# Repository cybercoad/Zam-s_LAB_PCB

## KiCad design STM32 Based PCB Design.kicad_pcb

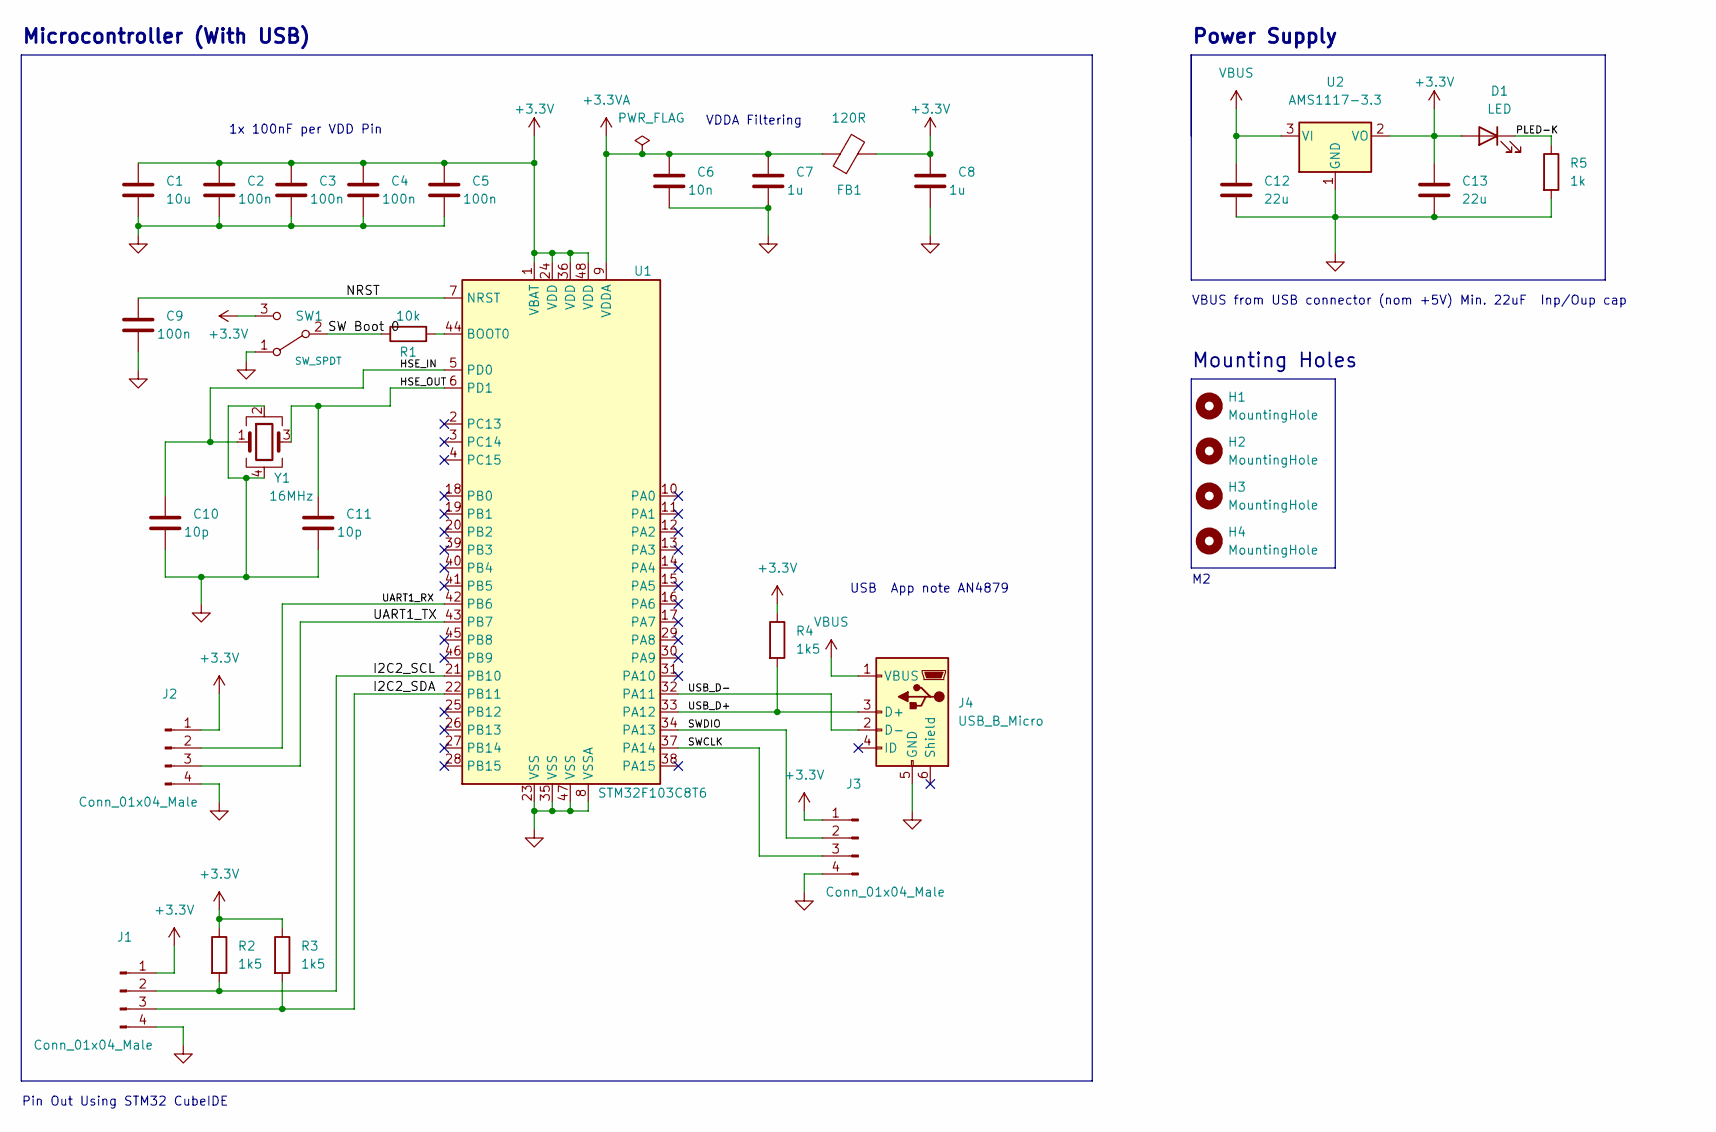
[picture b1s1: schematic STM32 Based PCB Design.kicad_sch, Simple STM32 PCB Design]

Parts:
C1: 10u; C_0603_1608Metric
C2, C3, C4, C5, C9: 100n; C_0402_1005Metric
C6: 10n; C_0402_1005Metric
C7, C8: 1u; C_0402_1005Metric
C10, C11: 10p; C_0402_1005Metric
C12, C13: 22u; C_0805_2012Metric
D1: LED; LED_0603_1608Metric
FB1: 120R; L_0603_1608Metric
H1, H2, H3, H4: MountingHole; MountingHole_2.2mm_M2
J1, J2, J3: Conn_01x04_Male; PinHeader_1x04_P2.54mm_Vertical
J4: USB_B_Micro; USB_Micro-B_Wuerth_629105150521
R1: 10k; R_0402_1005Metric
R2, R3, R4: 1k5; R_0402_1005Metric
R5: 1k; R_0402_1005Metric
SW1: SW_SPDT; SW_SPDT_PCM12
U1: STM32F103C8T6; LQFP-48_7x7mm_P0.5mm
U2: AMS1117-3.3; SOT-223-3_TabPin2
Y1: 16MHz; Crystal_SMD_3225-4Pin_3.2x2.5mm

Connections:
+3.3V: C1.1, C2.1, C3.1, C4.1, C5.1, C8.1, C13.1, D1.2 (A), FB1.2, J1.1, J2.1, J3.1, R2.1, R3.1, R4.1, SW1.3 (C), U1.1 (VBAT), U1.24 (VDD), U1.36 (VDD), U1.48 (VDD), U2.2 (VO)
+3.3VA: C6.1, C7.1, FB1.1, U1.9 (VDDA)
/HSE_IN: C10.1, U1.5 (PD0), Y1.1
/HSE_OUT: C11.1, U1.6 (PD1), Y1.3
/I2C2_SCL: J1.2, R2.2, U1.21 (PB10)
/I2C2_SDA: J1.3, R3.2, U1.22 (PB11)
/NRST: C9.1, U1.7 (NRST)
/PLED-K: D1.1 (K), R5.1
/SW Boot 0: R1.1, SW1.2 (B)
/SWCLK: J3.3, U1.37 (PA14)
/SWDIO: J3.2, U1.34 (PA13)
/UART1_RX: J2.2, U1.42 (PB6)
/UART1_TX: J2.3, U1.43 (PB7)
/USB_D+: J4.3 (D+), R4.2, U1.33 (PA12)
/USB_D-: J4.2 (D-), U1.32 (PA11)
GND: C1.2, C2.2, C3.2, C4.2, C5.2, C6.2, C7.2, C8.2, C9.2, C10.2, C11.2, C12.2, C13.2, J1.4, J2.4, J3.4, J4.5 (GND), R5.2, SW1.1 (A), U1.8 (VSSA), U1.23 (VSS), U1.35 (VSS), U1.47 (VSS), U2.1 (GND), Y1.2, Y1.4
unnamed: R1.2, U1.44 (BOOT0)
VBUS: C12.1, J4.1 (VBUS), U2.3 (VI)

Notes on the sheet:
VBUS from USB connector (nom +5V) Min. 22uF Inp/Oup cap
VDDA Filtering
Microcontroller (With USB)
Power Supply
Pin Out Using STM32 CubeIDE
USB App note AN4879
1x 100nF per VDD Pin
Mounting Holes

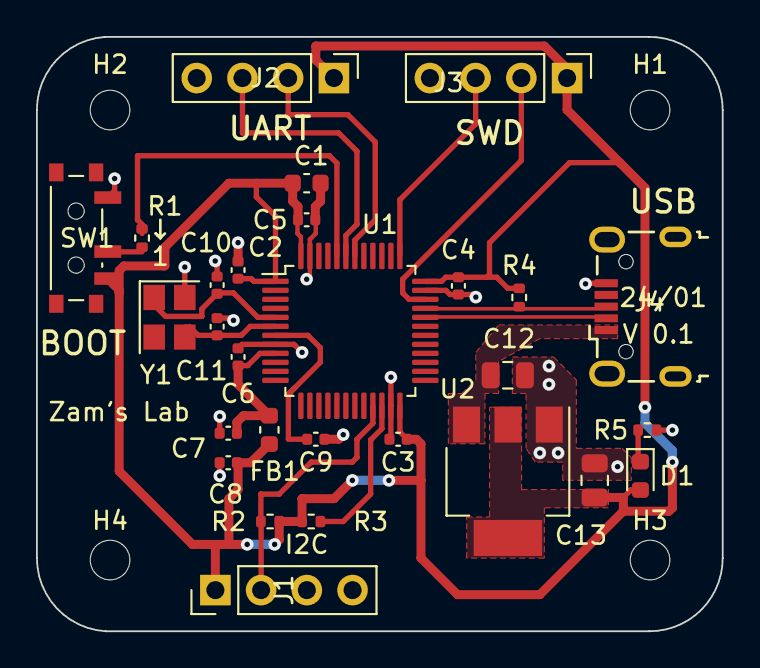
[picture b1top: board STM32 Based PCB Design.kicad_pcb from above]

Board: 2 copper layers, 38.1 x 33.0 mm, 32 parts (0 on the bottom side), 18 nets.

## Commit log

2024-12-04 Initial Design v.01
2024-12-04 Description of changes
